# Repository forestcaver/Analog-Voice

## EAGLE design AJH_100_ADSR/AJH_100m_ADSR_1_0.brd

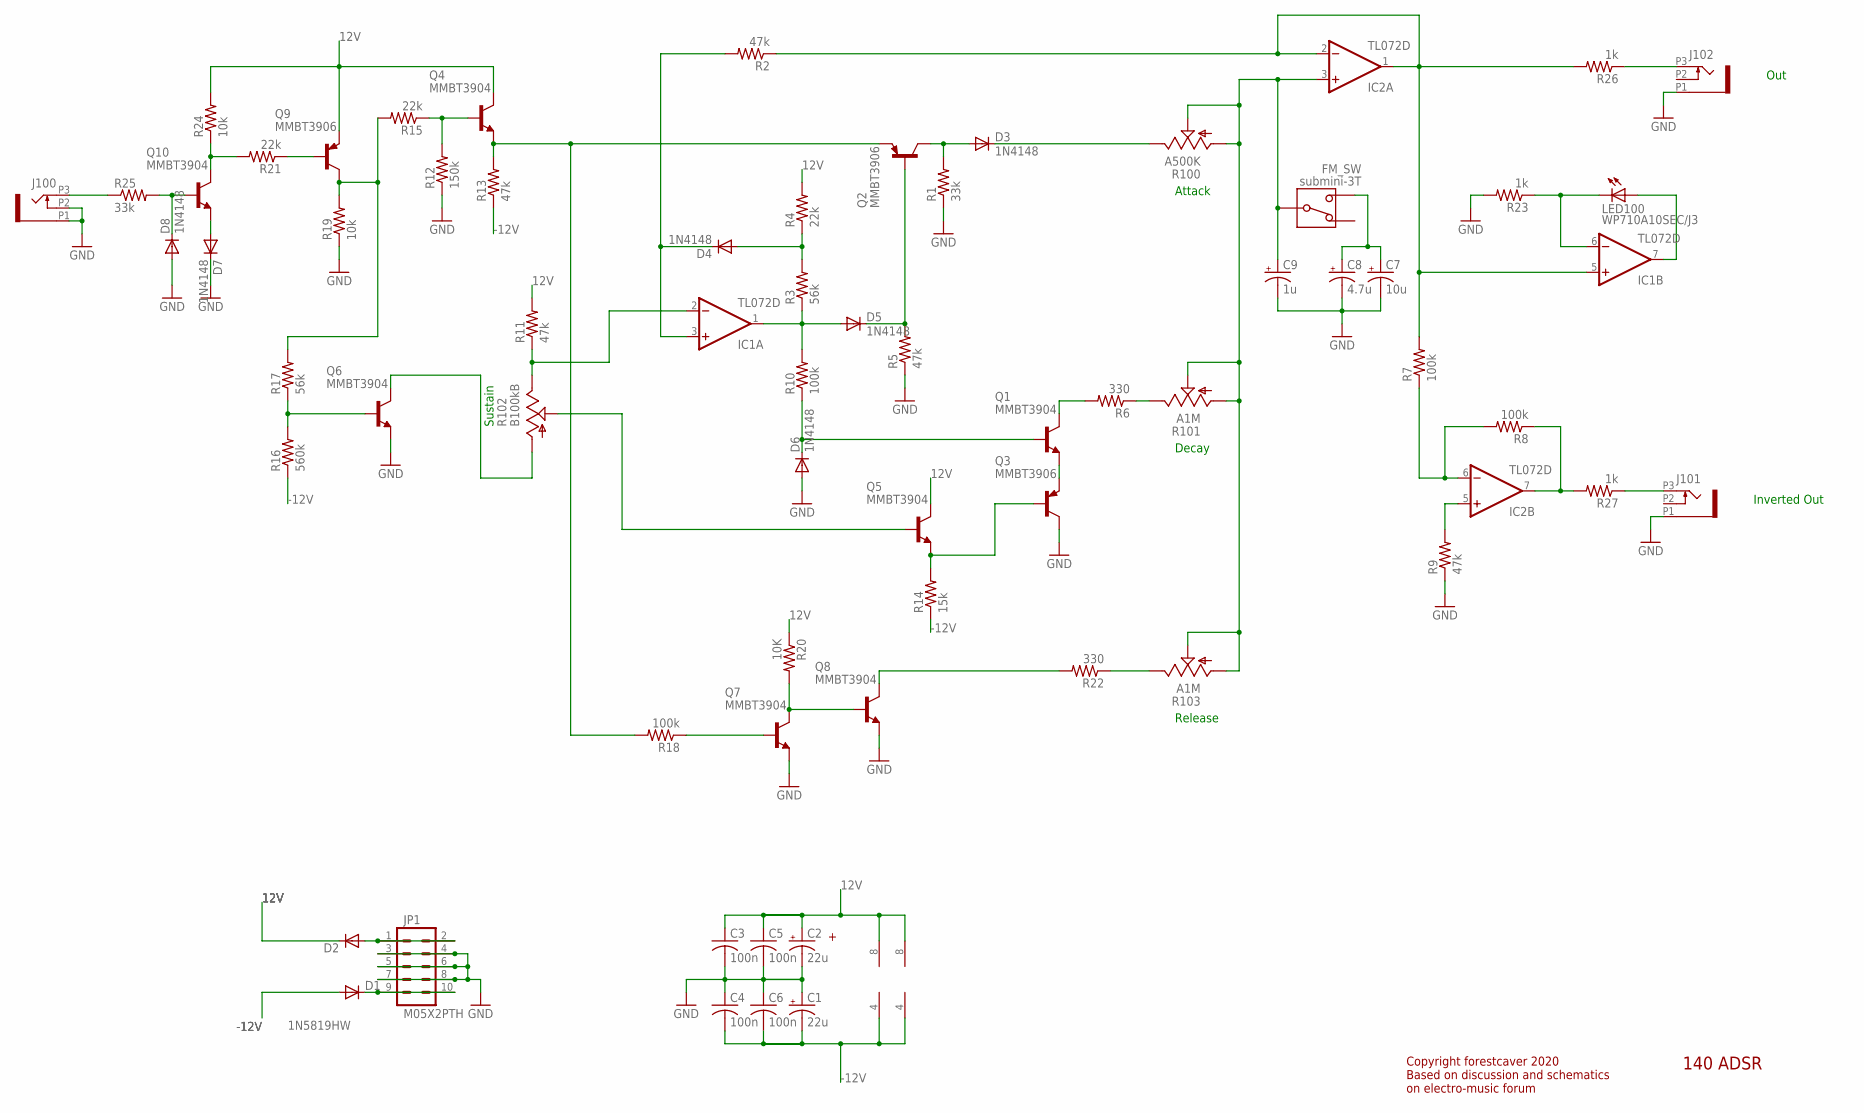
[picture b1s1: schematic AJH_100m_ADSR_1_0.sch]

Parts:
C1, C2: 22u; PANASONIC_B
C3, C4, C5, C6: 100n; C0603
C7: 10u; PANASONIC_B
C8: 4.7u; PANASONIC_B
C9: 1u; PANASONIC_B
D1, D2: 1N5819HW; SOD123
D3, D4, D5, D6, D7, D8: 1N4148; SOD323-W
FM_SW: submini-3T; SPDT-SUB
IC1, IC2: TL072D; SO08
J100, J101, J102: PJ301_THONKICONN6; WQP_PJ_301M6
JP1: M05X2PTH; AVR_ICSP
LED100: WP710A10SEC/J3; LED3MM
Q1, Q4, Q5, Q6, Q7, Q8, Q10: MMBT3904; SOT23-BEC
Q2, Q3, Q9: MMBT3906; SOT23-BEC
R1, R25: 33k; R0603
R2, R5, R9, R11, R13: 47k; R0603
R3, R17: 56k; R0603
R4, R15, R21: 22k; R0603
R6, R22: 330; R0603
R7, R8, R10, R18: 100k; R0603
R12: 150k; R0603
R14: 15k; R0603
R16: 560k; R0603
R19, R24: 10k; R0603
R20: 10K; R0603
R23, R26, R27: 1k; R0603
R100: A500K; ALPS_POT_VERTICAL
R101, R103: A1M; ALPS_POT_VERTICAL
R102: B100kB; ALPS_POT_VERTICAL

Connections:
12V: C2.+, C3.1, C5.1, D2.C, IC1.8 (V+), IC2.8 (V+), Q4.C, Q5.C, Q9.E, R4.2, R11.2, R20.1, R24.2
-12V: C1.-, C4.2, C6.2, D1.A, IC1.4 (V-), IC2.4 (V-), R13.1, R14.1, R16.1
GND: C1.+, C2.-, C3.2, C4.1, C5.2, C6.1, C7.-, C8.-, C9.-, D6.A, D7.C, D8.A, J100.P1 (1), J100.P2 (2), J101.P1 (1), J102.P1 (1), JP1.3, JP1.4, JP1.5, JP1.6, JP1.7, JP1.8, Q3.C, Q6.E, Q7.E, Q8.E, R1.1, R5.1, R9.1, R12.1, R19.1, R23.2
unnamed: IC1.6 (-IN), LED100.K (C), R23.1
unnamed: IC2.6 (-IN), R7.1, R8.2
unnamed: D4.A, R3.2, R4.1
unnamed: IC1.7 (OUT), LED100.A
unnamed: D2.A, JP1.1, JP1.2
unnamed: C7.+, C8.+, FM_SW.P$1
unnamed: IC1.5 (+IN), IC2.1 (OUT), IC2.2 (-IN), R2.1, R7.2, R26.2
unnamed: J102.P3 (3), R26.1
unnamed: IC2.7 (OUT), R8.1, R27.2
unnamed: J100.P3 (3), R25.1
unnamed: IC2.5 (+IN), R9.2
unnamed: D8.C, Q10.B, R25.2
unnamed: D7.A, Q10.E
unnamed: Q10.C, R21.2, R24.1
unnamed: Q9.B, R21.1
unnamed: D1.C, JP1.9, JP1.10
unnamed: Q9.C, R15.2, R17.2, R19.2
unnamed: Q2.E, Q4.E, R13.2, R18.2
unnamed: Q4.B, R12.2, R15.1
unnamed: Q6.C, R102.P$3 (A)
unnamed: Q6.B, R16.2, R17.1
unnamed: IC1.2 (-IN), R11.1, R102.P$1 (E)
unnamed: D4.C, IC1.3 (+IN), R2.2
unnamed: Q5.B, R102.P$2 (S)
unnamed: D3.A, Q2.C, R1.2
unnamed: D5.C, Q2.B, R5.2
unnamed: D5.A, IC1.1 (OUT), R3.1, R10.2
unnamed: D6.C, Q1.B, R10.1
unnamed: Q1.E, Q3.E
unnamed: Q1.C, R6.2
unnamed: D3.C, R100.P$1 (E)
unnamed: Q3.B, Q5.E, R14.2
unnamed: C9.+, FM_SW.P$2, IC2.3 (+IN), R100.P$2 (S), R100.P$3 (A), R101.P$2 (S), R101.P$3 (A), R103.P$2 (S), R103.P$3 (A)
unnamed: J101.P3 (3), R27.1
unnamed: R6.1, R101.P$1 (E)
unnamed: Q7.C, Q8.B, R20.2
unnamed: Q8.C, R22.2
unnamed: Q7.B, R18.1
unnamed: R22.1, R103.P$1 (E)

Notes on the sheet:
Sustain
Release
Decay
Attack
Out
Inverted Out
Copyright forestcaver 2020 Based on discussion and schematics on electro-music forum
140 ADSR

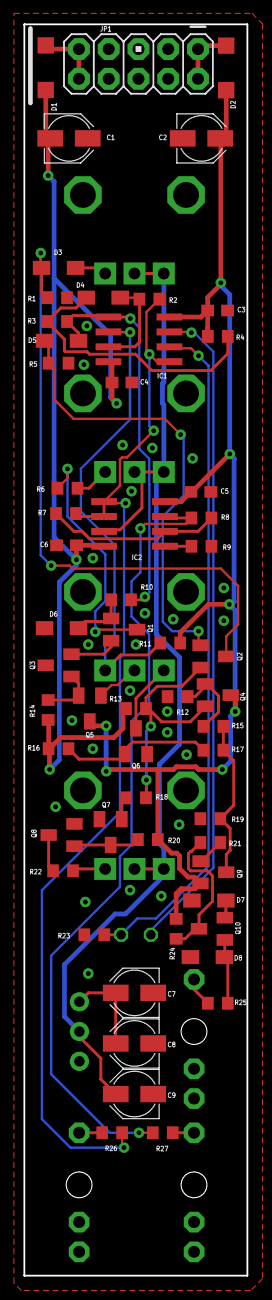
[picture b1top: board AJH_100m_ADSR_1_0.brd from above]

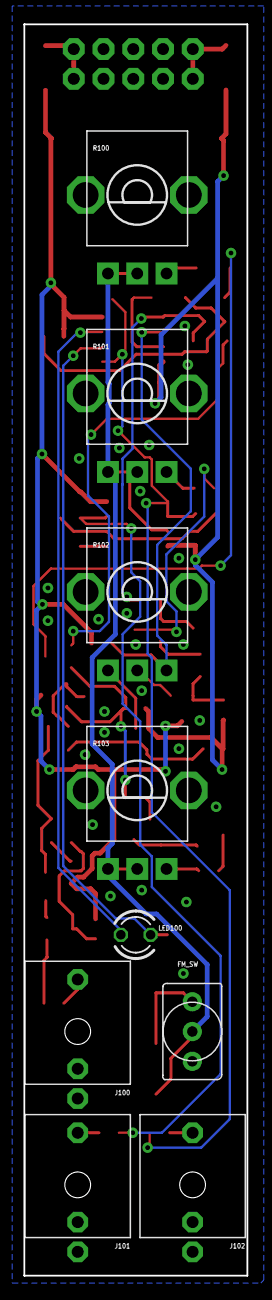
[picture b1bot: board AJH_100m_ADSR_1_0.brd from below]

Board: 2 copper layers, 19.0 x 106.8 mm, 66 parts (9 on the bottom side), 42 nets.

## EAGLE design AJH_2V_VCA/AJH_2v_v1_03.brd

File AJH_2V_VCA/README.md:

# 2V_VCA

Two sections of Mutable Instruments Veils. Multipe modules can be
chained together.

Tested and working.

CC-By-SA-4.0

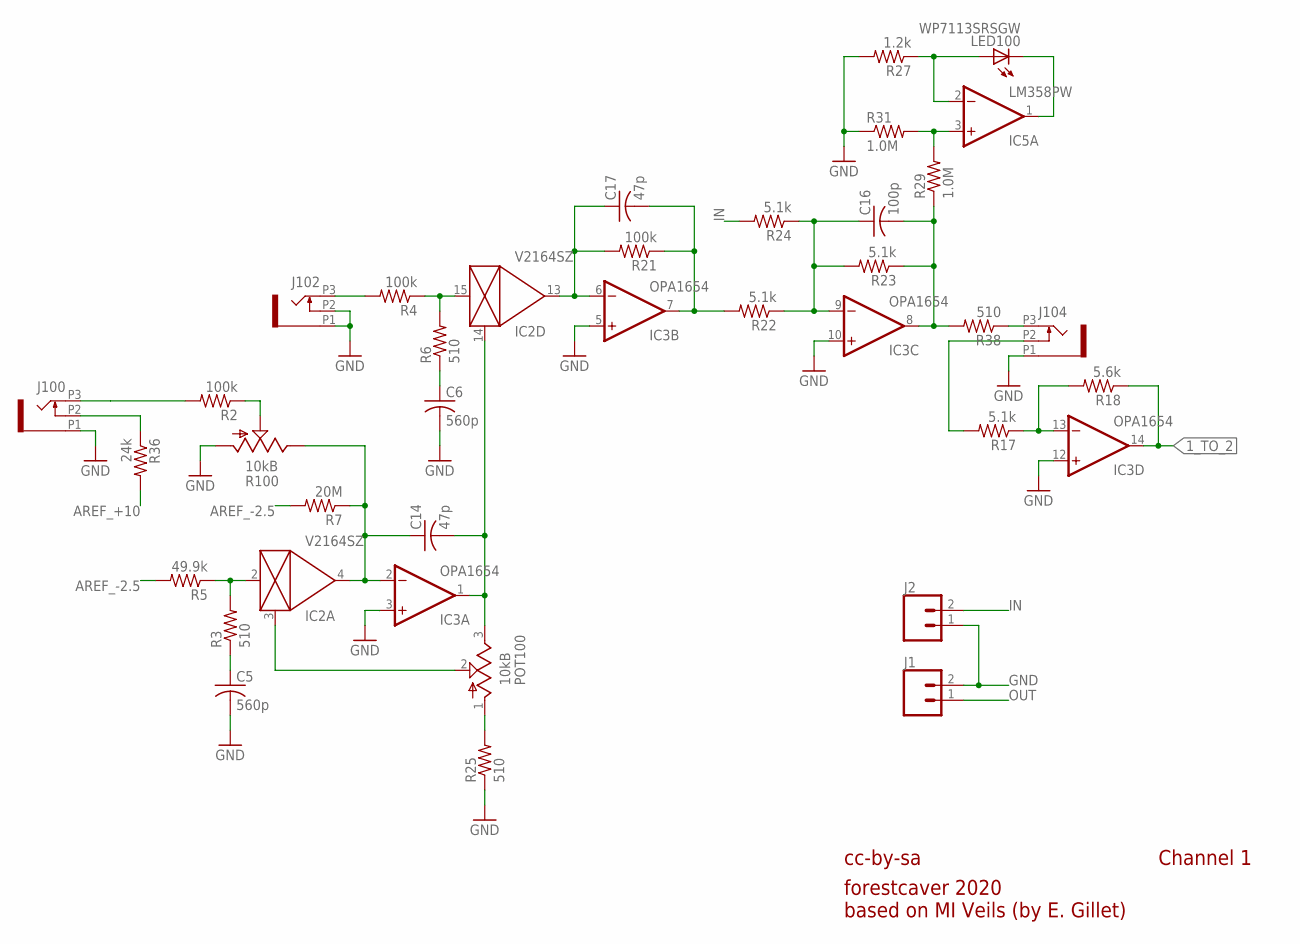
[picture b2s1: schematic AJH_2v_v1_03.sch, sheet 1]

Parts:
C5, C6: 560p; C0402
C14, C17: 47p; C0402
C16: 100p; C0402
IC2: V2164SZ; SOIC16N
IC3: OPA1654; TSSOP14
IC5: LM358PW; TSSOP8
J1, J2: CONN_02; 1X02
J100, J102, J104: PJ301_THONKICONN6; WQP_PJ_301M6
LED100: WP7113SRSGW; LED5MM
POT100: 10kB; ALPS_POT_NOHOLE
R2, R4, R21: 100k; R0402
R3, R6, R25, R38: 510; R0402
R5: 49.9k; R0402
R7: 20M; R0402
R17, R22, R23, R24: 5.1k; R0402
R18: 5.6k; R0402
R27: 1.2k; R0402
R29, R31: 1.0M; R0402
R36: 24k; R0402
R100: 10kB; ALPS_POT_VERTICAL_PS

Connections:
1_TO_2: IC3.14 (OUT), R18.1; also elsewhere on the board
AREF_+10: R36.2; also elsewhere on the board
AREF_-2.5: R5.2, R7.2; also elsewhere on the board
CV_IN_1: J100.P3 (3), R2.2
FOO: IC2.2 (IN), R3.2, R5.1
GND: C5.2, C6.2, IC3.3 (+IN), IC3.5 (+IN), IC3.10 (+IN), IC3.12 (+IN), J1.2, J2.1, J100.P1 (1), J102.P1 (1), J102.P2 (2), J104.P1 (1), R25.1, R27.2, R31.1, R100.P$3 (A); also elsewhere on the board
IN: J2.2, R24.2
unnamed: IC5.3 (+IN), R29.2, R31.2
unnamed: J104.P3 (3), R38.1
unnamed: IC2.3 (CTRL), POT100.2 (W)
unnamed: C16.1, IC3.9 (-IN), R22.1, R23.2, R24.1
unnamed: R2.1, R100.P$2 (S)
unnamed: POT100.1 (A), R25.2
unnamed: IC5.1 (OUT), LED100.K (C)
unnamed: IC5.2 (-IN), LED100.A, R27.1
unnamed: C5.1, R3.1
unnamed: J100.P2 (2), R36.1
unnamed: IC3.13 (-IN), R17.1, R18.2
unnamed: J104.P2 (2), R17.2
unnamed: C6.1, R6.1
unnamed: C14.1, IC2.4 (OUT), IC3.2 (-IN), R7.1, R100.P$1 (E)
unnamed: J102.P3 (3), R4.2
unnamed: IC2.15 (IN), R4.1, R6.2
unnamed: C14.2, IC2.14 (CTRL), IC3.1 (OUT), POT100.3 (B)
unnamed: C17.1, IC2.13 (OUT), IC3.6 (-IN), R21.2
unnamed: C17.2, IC3.7 (OUT), R21.1, R22.2
OUT: J1.1; also elsewhere on the board
OUT1: C16.2, IC3.8 (OUT), R23.1, R29.1, R38.2

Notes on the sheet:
cc-by-sa
Channel 1
forestcaver 2020 based on MI Veils (by E. Gillet)

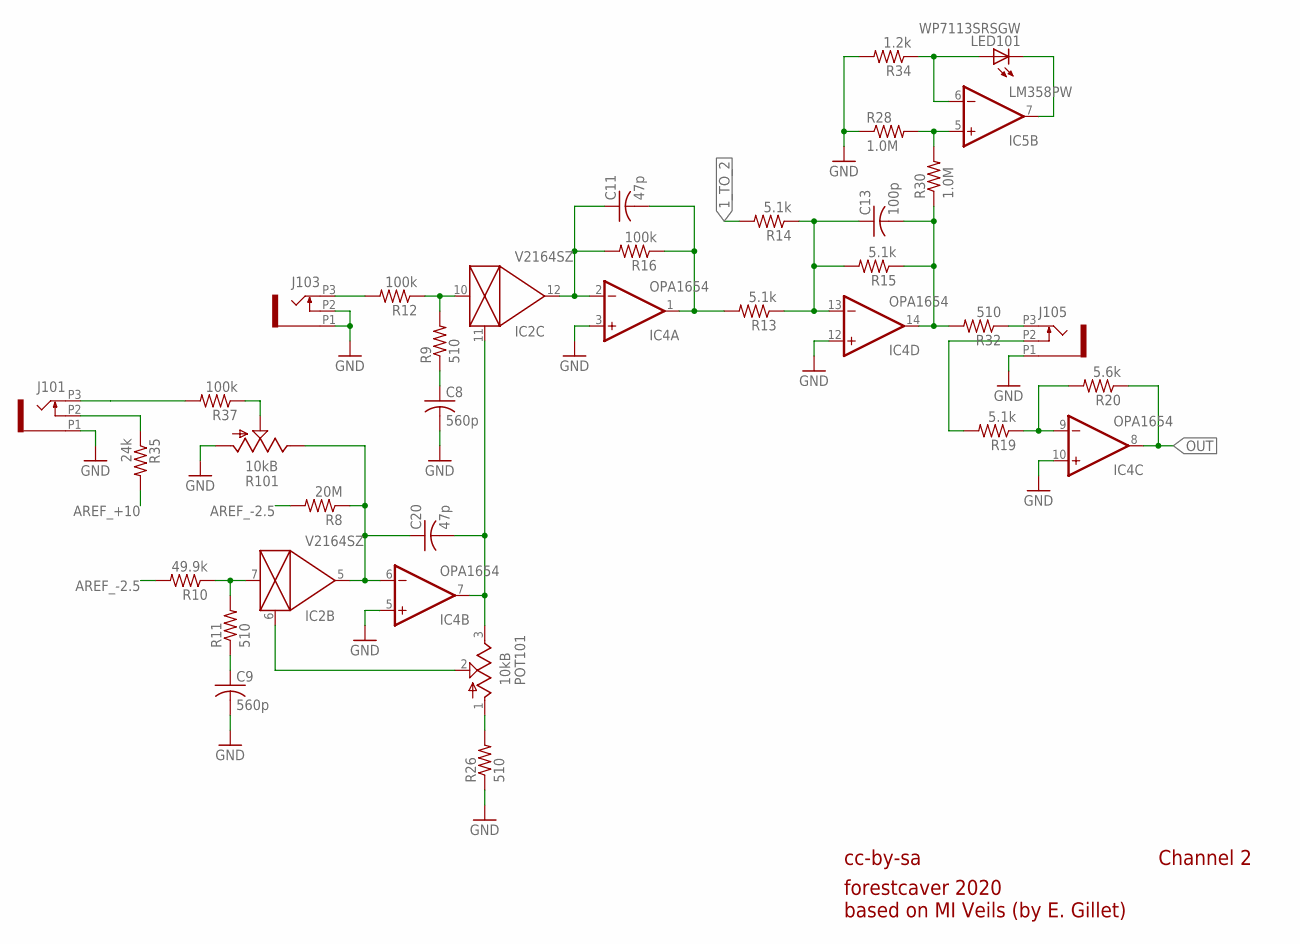
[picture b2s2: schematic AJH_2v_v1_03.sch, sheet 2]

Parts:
C8, C9: 560p; C0402
C11, C20: 47p; C0402
C13: 100p; C0402
IC2: V2164SZ; SOIC16N
IC4: OPA1654; TSSOP14
IC5: LM358PW; TSSOP8
J101, J103, J105: PJ301_THONKICONN6; WQP_PJ_301M6
LED101: WP7113SRSGW; LED5MM
POT101: 10kB; ALPS_POT_NOHOLE
R8: 20M; R0402
R9, R11, R26, R32: 510; R0402
R10: 49.9k; R0402
R12, R16, R37: 100k; R0402
R13, R14, R15, R19: 5.1k; R0402
R20: 5.6k; R0402
R28, R30: 1.0M; R0402
R34: 1.2k; R0402
R35: 24k; R0402
R101: 10kB; ALPS_POT_VERTICAL_PS

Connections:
1_TO_2: R14.2; also elsewhere on the board
AREF_+10: R35.2; also elsewhere on the board
AREF_-2.5: R8.2, R10.2; also elsewhere on the board
FOO1: IC2.7 (IN), R10.1, R11.2
GND: C8.2, C9.2, IC4.3 (+IN), IC4.5 (+IN), IC4.10 (+IN), IC4.12 (+IN), J101.P1 (1), J103.P1 (1), J103.P2 (2), J105.P1 (1), R26.1, R28.1, R34.2, R101.P$3 (A); also elsewhere on the board
unnamed: J103.P3 (3), R12.2
unnamed: IC5.5 (+IN), R28.2, R30.2
unnamed: J105.P3 (3), R32.1
unnamed: C8.1, R9.1
unnamed: IC2.10 (IN), R9.2, R12.1
unnamed: IC2.6 (CTRL), POT101.2 (W)
unnamed: C13.1, IC4.13 (-IN), R13.1, R14.1, R15.2
unnamed: C20.2, IC2.11 (CTRL), IC4.7 (OUT), POT101.3 (B)
unnamed: POT101.1 (A), R26.2
unnamed: IC5.7 (OUT), LED101.K (C)
unnamed: IC5.6 (-IN), LED101.A, R34.1
unnamed: IC4.9 (-IN), R19.1, R20.2
unnamed: J105.P2 (2), R19.2
unnamed: C11.2, IC4.1 (OUT), R13.2, R16.1
unnamed: R37.1, R101.P$2 (S)
unnamed: C9.1, R11.1
unnamed: C20.1, IC2.5 (OUT), IC4.6 (-IN), R8.1, R101.P$1 (E)
unnamed: J101.P3 (3), R37.2
unnamed: C11.1, IC2.12 (OUT), IC4.2 (-IN), R16.2
unnamed: J101.P2 (2), R35.1
OUT: IC4.8 (OUT), R20.1; also elsewhere on the board
OUT2: C13.2, IC4.14 (OUT), R15.1, R30.1, R32.2

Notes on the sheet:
cc-by-sa
forestcaver 2020 based on MI Veils (by E. Gillet)
Channel 2

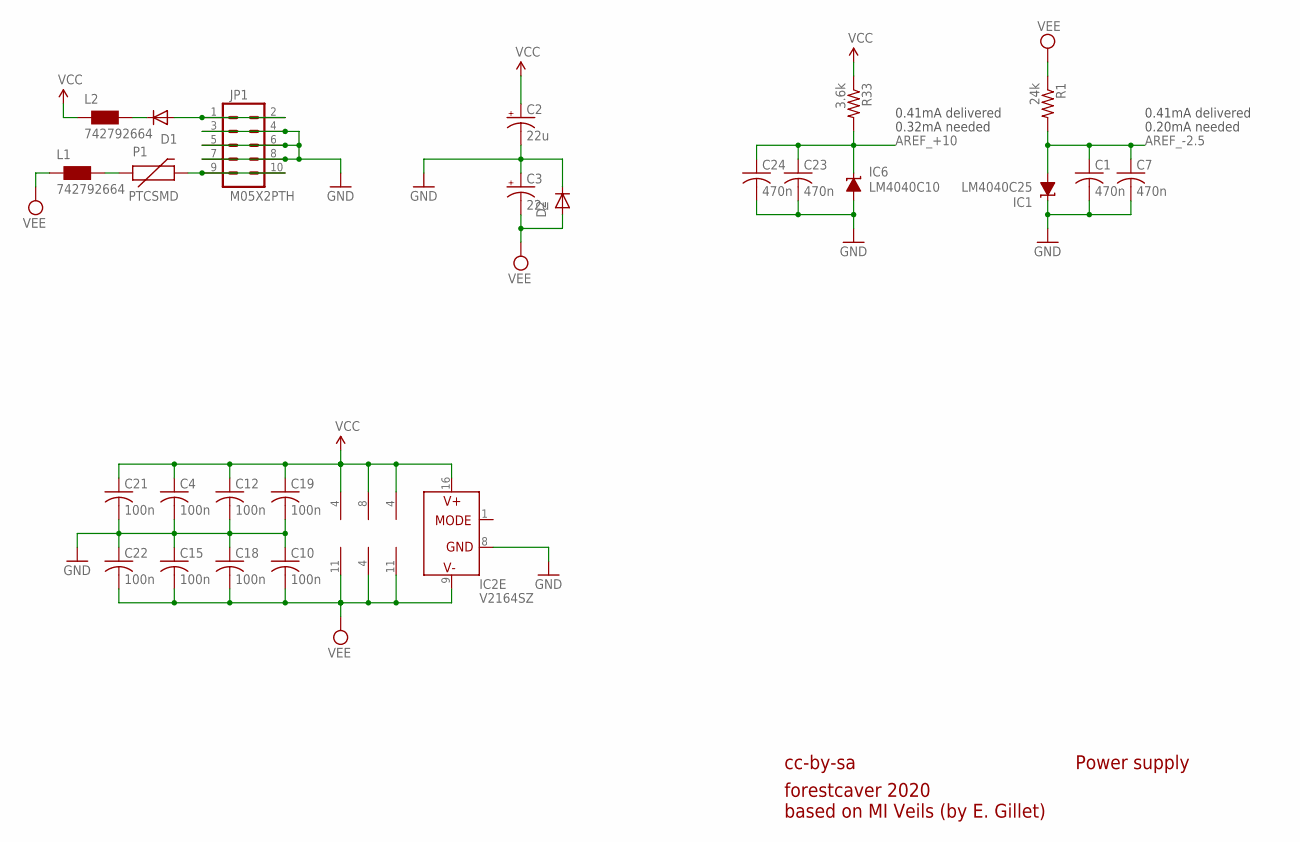
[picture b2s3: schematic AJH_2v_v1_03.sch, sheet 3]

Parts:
C1, C7, C23, C24: 470n; C0402
C2, C3: 22u; PANASONIC_B
C4, C10, C12, C15, C18, C19, C21, C22: 100n; C0402
D1, D2: 1N5819HW; SOD123
IC1: LM4040C25; DBZ_R-PDSO-G3
IC2: V2164SZ; SOIC16N
IC3, IC4: OPA1654; TSSOP14
IC5: LM358PW; TSSOP8
IC6: LM4040C10; DBZ_R-PDSO-G3
JP1: M05X2PTH; AVR_ICSP
L1, L2: 742792664; 0603
P1: PTCSMD; PTC-1206
R1: 24k; R0402
R33: 3.6k; R0402

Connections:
AREF_+10: C23.1, C24.1, IC6.1 (C), R33.2; also elsewhere on the board
AREF_-2.5: C1.1, C7.1, IC1.2 (A), R1.2; also elsewhere on the board
GND: C1.2, C2.-, C3.+, C4.2, C7.2, C10.1, C12.2, C15.1, C18.1, C19.2, C21.2, C22.1, C23.2, C24.2, D2.C, IC1.1 (C), IC2.8 (GND), IC6.2 (A), JP1.3, JP1.4, JP1.5, JP1.6, JP1.7, JP1.8; also elsewhere on the board
unnamed: D1.A, JP1.1, JP1.2
unnamed: JP1.9, JP1.10, P1.2
unnamed: L1.2, P1.1
unnamed: D1.C, L2.2
VCC: C2.+, C4.1, C12.1, C19.1, C21.1, IC2.16 (V+), IC3.4 (V+), IC4.4 (V+), IC5.8 (V+), L2.1, R33.1
VEE: C3.-, C10.2, C15.2, C18.2, C22.2, D2.A, IC2.9 (V-), IC3.11 (V-), IC4.11 (V-), IC5.4 (V-), L1.1, R1.1

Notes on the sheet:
cc-by-sa
Power supply
0.41mA delivered
0.20mA needed
0.32mA needed
forestcaver 2020 based on MI Veils (by E. Gillet)

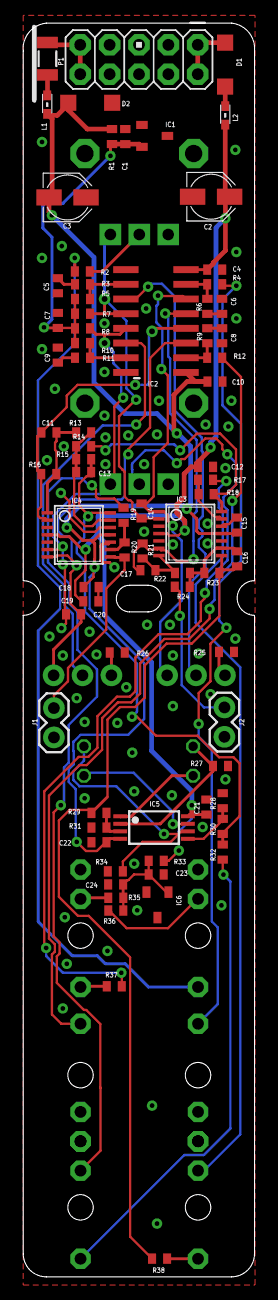
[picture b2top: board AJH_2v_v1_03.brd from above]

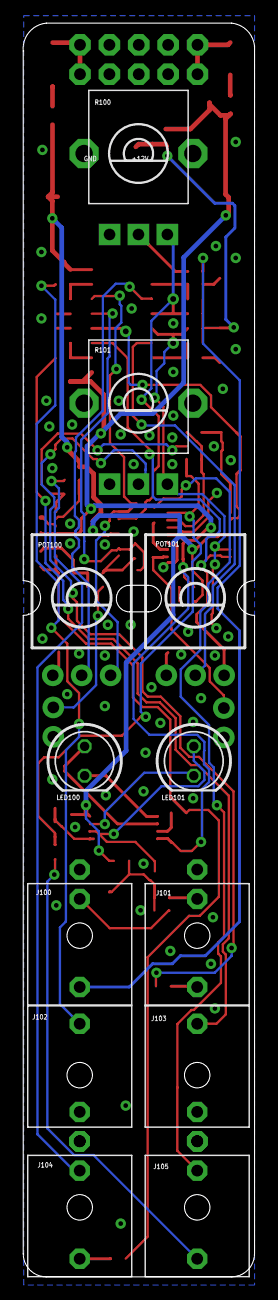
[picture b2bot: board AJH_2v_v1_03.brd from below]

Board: 2 copper layers, 20.0 x 108.4 mm, 88 parts (12 on the bottom side), 56 nets.

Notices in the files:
parts and their libraries:
SparkFun-Connectors: Licensing: Creative Commons ShareAlike 4.0 International - https://creativecommons.org/licenses/by-sa/4.0
